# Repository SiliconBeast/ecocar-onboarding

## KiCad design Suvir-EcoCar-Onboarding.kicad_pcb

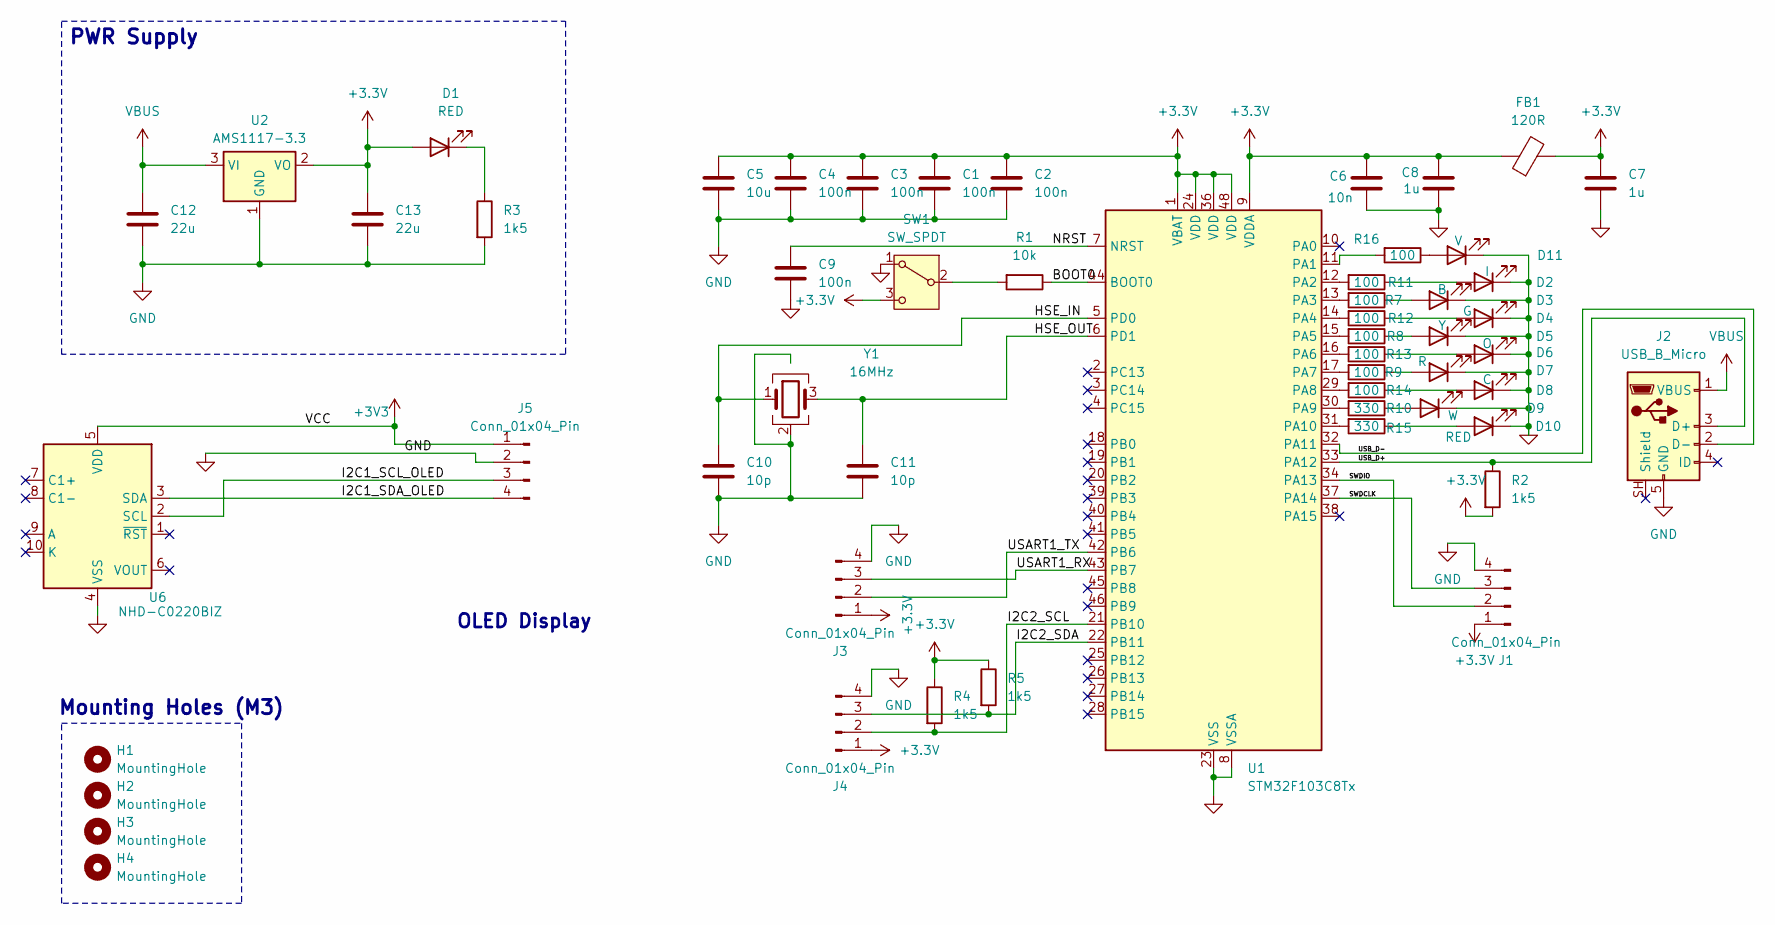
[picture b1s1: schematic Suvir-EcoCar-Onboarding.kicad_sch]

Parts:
C1, C2, C3, C4, C9: 100n; C_0402_1005Metric
C5: 10u; C_0603_1608Metric
C6: 10n; C_0402_1005Metric
C7, C8: 1u; C_0402_1005Metric
C10, C11: 10p; C_0402_1005Metric
C12, C13: 22u; C_0805_2012Metric
D1, D10: RED; LED_0603_1608Metric
D2: I; LED_0603_1608Metric
D3: B; LED_0603_1608Metric
D4: G; LED_0603_1608Metric
D5: Y; LED_0603_1608Metric
D6: O; LED_0603_1608Metric
D7: R; LED_0603_1608Metric
D8: C; LED_0603_1608Metric
D9: W; LED_0603_1608Metric
D11: V; LED_0603_1608Metric
FB1: 120R; L_0603_1608Metric
H1, H2, H3, H4: MountingHole; MountingHole_3.2mm_M3
J1, J3, J4, J5: Conn_01x04_Pin; PinHeader_1x04_P2.54mm_Vertical
J2: USB_B_Micro; USB_Micro-B_Wuerth_629105150521
R1: 10k; R_0402_1005Metric
R2, R3, R4, R5: 1k5; R_0402_1005Metric
R7, R8, R9, R11, R12, R13, R14, R16: 100; R_0402_1005Metric
R10, R15: 330; R_0402_1005Metric
SW1: SW_SPDT; SW_SPDT_PCM12
U1: STM32F103C8Tx; LQFP-48_7x7mm_P0.5mm
U2: AMS1117-3.3; SOT-223-3_TabPin2
U6: NHD-C0220BIZ; NHD-C0220BiZ
Y1: 16MHz; Crystal_SMD_3225-4Pin_3.2x2.5mm

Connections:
+3.3V: C1.1, C2.1, C3.1, C4.1, C5.1, C6.1, C7.1, C8.1, C13.1, D1.2 (A), FB1.1, FB1.2, J1.1, J3.1, J4.1, R2.2, R4.1, R5.1, SW1.3 (C), U1.1 (VBAT), U1.9 (VDDA), U1.24 (VDD), U1.36 (VDD), U1.48 (VDD), U2.2 (VO)
+3V3: J5.1, U6.5 (VDD)
/BOOT0: R1.1, U1.44 (BOOT0)
/HSE_IN: C10.1, U1.5 (PD0), Y1.1
/HSE_OUT: C11.1, U1.6 (PD1), Y1.3
/I2C1_SCL_OLED: J5.3, U6.2 (SCL)
/I2C1_SDA_OLED: J5.4, U6.3 (SDA)
/I2C2_SCL: J4.2, R4.2, U1.21 (PB10)
/I2C2_SDA: J4.3, R5.2, U1.22 (PB11)
/NRST: C9.1, U1.7 (NRST)
/SWDCLK: J1.3, U1.37 (PA14)
/SWDIO: J1.2, U1.34 (PA13)
/USART1_RX: J3.3, U1.43 (PB7)
/USART1_TX: J3.2, U1.42 (PB6)
/USB_D+: J2.3 (D+), R2.1, U1.33 (PA12)
/USB_D-: J2.2 (D-), U1.32 (PA11)
GND: C1.2, C2.2, C3.2, C4.2, C5.2, C6.2, C7.2, C8.2, C9.2, C10.2, C11.2, C12.2, C13.2, D2.1 (K), D3.1 (K), D4.1 (K), D5.1 (K), D6.1 (K), D7.1 (K), D8.1 (K), D9.1 (K), D10.1 (K), D11.1 (K), J1.4, J2.5 (GND), J3.4, J4.4, J5.2, R3.2, SW1.1 (A), U1.8 (VSSA), U1.23 (VSS), U1.35 (VSS), U1.47 (VSS), U2.1 (GND), U6.4 (VSS), Y1.2, Y1.4
unnamed: D1.1 (K), R3.1
unnamed: D2.2 (A), R11.1
unnamed: D3.2 (A), R7.1
unnamed: D4.2 (A), R12.1
unnamed: D5.2 (A), R8.1
unnamed: D6.2 (A), R13.1
unnamed: D7.2 (A), R9.1
unnamed: D8.2 (A), R14.1
unnamed: D9.2 (A), R10.1
unnamed: D10.2 (A), R15.1
unnamed: D11.2 (A), R16.1
unnamed: R1.2, SW1.2 (B)
unnamed: R16.2, U1.11 (PA1)
unnamed: R11.2, U1.12 (PA2)
unnamed: R7.2, U1.13 (PA3)
unnamed: R12.2, U1.14 (PA4)
unnamed: R8.2, U1.15 (PA5)
unnamed: R13.2, U1.16 (PA6)
unnamed: R9.2, U1.17 (PA7)
unnamed: R14.2, U1.29 (PA8)
unnamed: R10.2, U1.30 (PA9)
unnamed: R15.2, U1.31 (PA10)
VBUS: C12.1, J2.1 (VBUS), U2.3 (VI)

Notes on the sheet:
Mounting Holes (M3)
OLED Display
PWR Supply

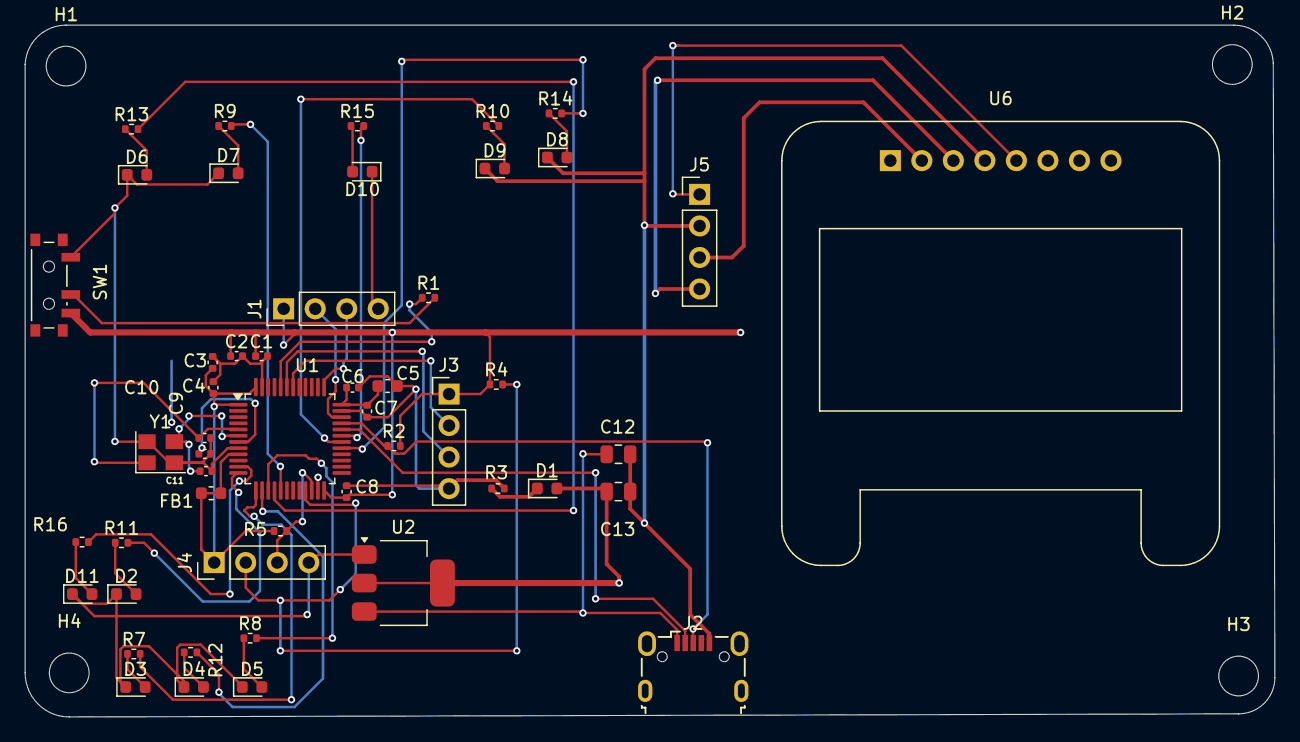
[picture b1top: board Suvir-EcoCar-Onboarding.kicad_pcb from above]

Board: 2 copper layers, 100.7 x 55.7 mm, 54 parts (0 on the bottom side), 40 nets.

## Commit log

2026-03-31 made changes wrt routing
2026-04-04 final changes
